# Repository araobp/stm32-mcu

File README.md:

# Application components for STMicro STM32 MCUs

Toolchain: Migrating from TrueSTUDIO+CubeMX to [STM32CubeIDE](https://www.st.com/en/development-tools/stm32cubeide.html)

## Common libraries

### [NUCLEO-F401RE](http://www.st.com/en/evaluation-tools/nucleo-f401re.html) board

- [DCT Type-II implementation on CMSIS-DSP (also works on L4)](./NUCLEO-F401RE/DCT) including a zigzag scan utility function.

## Application components

### [NUCLEO-F401RE](http://www.st.com/en/evaluation-tools/nucleo-f401re.html) board

- [Thermography (infrared array sensor) and rock-paper-scissors recogniton with Keras/TensorFlow](./NUCLEO-F401RE/Thermography)
- [X-CUBE-AI (ML inference on MCU with 2D images from an infrared array sensor)](./NUCLEO-F401RE/AI)
- [X-CUBE-BLE1 (BLE)](./NUCLEO-F401RE/BLE)

### [NUCLEO-L476RG](http://www.st.com/en/evaluation-tools/nucleo-l476rg.html) board

- [HelloWorld](./NUCLEO-L476RG/HelloWorld)
- [GPIO_Interrupt](./NUCLEO-L476RG/GPIO_Interrupt)
- [Clock](./NUCLEO-L476RG/Clock/README.md)
- [CAN](./NUCLEO-L476RG/CAN/README.md)
- [MEMSMIC(MEMS mic expansion board)](./NUCLEO-L476RG/MEMSMIC/README.md)
- [ADC with DMA](./NUCLEO-L476RG/ADC/README.md)
- [DAC with triangular wave and sine wave](./NUCLEO-L476RG/DAC/README.md)
- [Mic->ADC->DAC pipeline](./NUCLEO-L476RG/Mic_ADC_DAC/README.md)
- [Sound Effector](./NUCLEO-L476RG/Sound_Effector)
- [Chirp compression](./NUCLEO-L476RG/Chirp_Compression)

### [NUCLEO-F401RE](http://www.st.com/en/evaluation-tools/nucleo-f401re.html) and [NUCLEO-L476RG](http://www.st.com/en/evaluation-tools/nucleo-l476rg.html) boards

#### Dynamic NFC tags
- [ST25DV04K (NFC) on F401RE](./NUCLEO-F401RE/NFC)
- [ST25DV04K (NFC) on L476RG](./NUCLEO-L476RG/NFC) 

### [STM32F4 Discovery](http://www.st.com/en/evaluation-tools/stm32f4discovery.html) board

- [Camera (CMOS image sensor OV7670)](./STM32F4-Discovery/Camera)
- [BlueSwitch](./STM32F4-Discovery/BlueSwitch)
- [HelloWorld](./STM32F4-Discovery/HelloWorld)
- [LED_blinking](./STM32F4-Discovery/LED_blinking)
- [PWM-output](./STM32F4-Discovery/PWM-output)
- [AudioWeaver](./STM32F4-Discovery/AudioWeaver)

#### printf issue

I managed to support printf on USART2.

Physical configuration:

```
STM32F407
               +------------+
            X 5V            |
GND     ----- GND  FTDI     |
PA3(RX) ----- TX  USB-UART  ===== USB ======> PC
PA2(TX) ----- RX  converter |
               +------------+
```

Include the following snippet in main.c to support printf:

```
int _write(int file, char *pbuf, int len)
{
  HAL_UART_Transmit(&huart2, (uint8_t *)pbuf, len, 1000);
  return len;
}
```

#### PWM test

PWM output (100Hz, 50% duty) to PA8:

## Tips

- [CMSIS DSP RFFT pitfalls](./tips/CMSIS_DSP_RFFT.md)
- [Enabling DSP on STM32](./tips/ENABLE_DSP.md)
- [PCM data resolution on STM32L4 DFSDM](./tips/RESOLUTION.md)
- [Enabling printf on STM32](./tips/ENABLE_PRINTF.md)

## References

### STM32L476 Nucleo-64

- [Schematics](http://www.st.com/resource/en/schematic_pack/nucleo_64pins_sch.zip)
- [Datasheet](http://www.st.com/resource/en/datasheet/stm32l476je.pdf)

### STM32F4 Discovery board

- [Schematics](http://www.st.com/resource/en/schematic_pack/stm32f4discovery_sch.zip)
- [Datasheet](http://www.st.com/resource/en/datasheet/dm00037051.pdf)

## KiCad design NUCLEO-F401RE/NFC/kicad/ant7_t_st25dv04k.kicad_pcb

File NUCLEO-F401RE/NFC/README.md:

# ST25DV04K

This chip ["ST25DV04K"](https://www.st.com/en/nfc/st25dv-i2c-series-dynamic-nfc-tags.html) from STMicro can be used for showing an internal status of a home appliance to the user's smart phone.

[Note] I lately migrated from TrueSTUIO+CubeMX to CubeIDE. The quality of CubeIDE 1.0.0 is NOT good. Some precautions I learned by doing for 24 hours wasting a lot of time:
- Always start a new STM32 project from CubeIDE, do not generate code from CubeMX.
- Do not regenerate code on CubeIDE -- if you need some config modifications, create a new project on CubeIDE again, although it is a waste of time.
- Otherwise, you will face a lot of errors at a build time or a debug time, including communication errors with the targe board over ST-Link.

## Typical operations (my guess)

[1] A smart phone initiates a service.

```
   Sleeping                                         
    [STM32]          [ST25DV]<---RF----[Smart phone] User
      ^               GPO                           
      |                |
      +----------------+
           Interrupt
```

[1b(optional)] The device notifies a BLE central of the RF field change event 

```
       +--------NOTIFY---------------------------->[BLE central]
       |
   [RN4020]                                         
    [STM32]          [ST25DV]<---RF----[Smart phone] User
```

[2] The device prepares a service for the user in a very short time.

```
[Local service function]
       |
       v
    [STM32]          [ST25DV]<---RF----[Smart phone] User
Service preparation  
```

[3] The device provides a service URL to the smartphone.

```
    [STM32]---I2C--->[ST25]----RF--->[Smart phone]----GET---->[Web application server]
                             (URL)
```

[4] The smartphone fetchs the page from a web server.

```
    [STM32]          [ST25]          [Smart phone]<---200 OK--[Web application server]
```

Note: the last data written on the tag (e.g., on EEPROM) will remain even if the battery dies.

## Internal status of home appliance

- Initial setup: URL of its startup manual page
- Serial number (fixed number): URL of a user registration page
- Some additional reference info (content ID) to a base URL: content ID shown on a digital signage currently
- Error code: URL of its trouble shooting page
- etc

In this project, I only support a serial number that is incremented every time the user hold his or her smart phone over the NFC tag. In case of the signage use case, content ID is appended to its base URL as "&ref=".

## Parts

- [Host MCU: NUCLEO F401RE](https://www.st.com/en/evaluation-tools/nucleo-f401re.html)
- [NFC tag: X-NUCLEO-NFC04A1(ST25DV04K)](https://www.st.com/en/ecosystems/x-nucleo-nfc04a1.html)
- [NFC tag: ANT7-T-ST25DV04K](https://www.st.com/en/evaluation-tools/ant7-t-st25dv04k.html)

## Code

### MCU with ST25DV

IDE: CubeIDE from STMicro.

==> **[Code](./stm32)**

- The code supports power management for the MCU.
- The code puts the MCU into sleep after start up, so CubeIDE cannot communicate with the MCU. In this case, hold a smart phone over the antenna to keep the MCU awaken.
- To disable the power management (to use GPO on PA9 as an interrupt to signal RF change to MCU), just comment out the following line:

main.c
```
#define SLEEP_ENABLED
```

**UART commands**

|Command                          |Description                        |
|---------------------------------|-----------------------------------|
|.l                               |Lock RF write (default)            |
|.u                               |Unlock RF write                    |
|.r                               |Reset (and clear EEPROM)           |
|<base url w/o protocol>?loc=<loc>|Write base URL to Area 2 on EEPROM |

Note: The current implementation of local service function just copies the base URL with a serial number, as an internal status of a home appliance, appended to Area 1 on EEPROM.

### HTTPS server for testing the device

==> **[Code](./webapp)**

### Home appliances

==> **[Code](./home_appliances)**

### Arduino shield of ANT7-T-ST25DV04K

I refered to the schematic of X-NUCLEO-NFC04A1(ST25DV04K) to design Arduino shield for ANT7-T-ST25DV04K with some modifications as follows:
- I omitted some small stuff such as bypass capacitors, because the board size is small.
- I chose 10k ohm pull-up registors for I2C. I think 10k ohm is relatively large, but it should work at 400kHz of SCL clock cycle in my experience.
- I chose a 51k ohm pull-up registor for open-drain GPO.

==> **[Circuit](./kicad/ant7_t_st25dv04k.pdf)**

==> **[Universal board](./kicad/arduino_shield_ant7_t_st25dv04k.pdf)**

## A bug in X-CUBE-NFC4/CubeMX

BSP folder is removed whenever code is generated by CubeMX after the initial generation. Copy BSP into the folder manually to cope with the problem.

## Future direction

["ADUX1020"](https://www.analog.com/en/products/adux1020.html) from Analog Devices is very interesting as a very small contactless gester sensing device in combination with dynamic NFC tag (not limited to STMicro's products but also from other makers such as NXP or SONY).

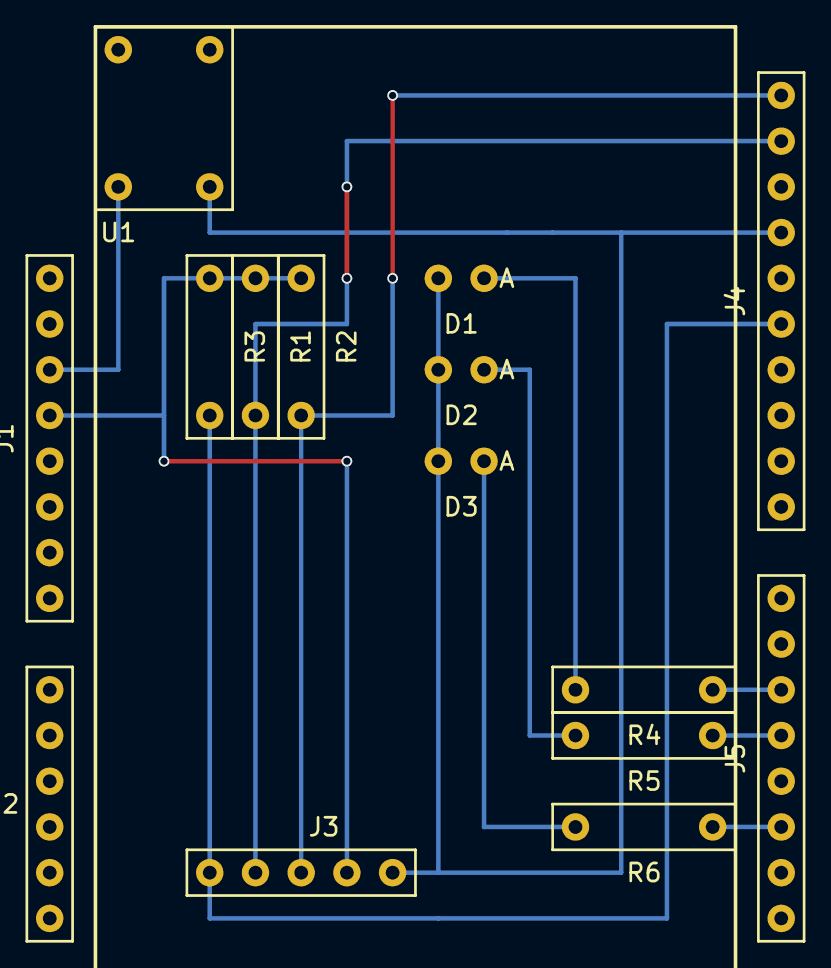
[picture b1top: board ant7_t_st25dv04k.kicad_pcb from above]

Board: 2 copper layers, 15 parts (0 on the bottom side), 12 nets.

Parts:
D1: LED GREEN; LED
D2: LED BLUE; LED
D3: LED RED; LED
J1, J5: Conn_01x08_Male; Pin Header 8P
J2: Conn_01x06_Male; Pin Header 6P
J3: Conn_01x05_Male; Pin_Header_5P
J4: Conn_01x10_Male; Pin Header 10P
R1, R2, R6: 10k; Register
R3, R4, R5: 51k; Register
U1: tactile_sw; tactile_sw_4p

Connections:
+3V3: J1.4, J3.2, R1.1, R2.1, R3.1
GND: D1.1, D2.1, D3.1, J3.1, J4.4, U1.2
unnamed: D1.2, R4.2
unnamed: D2.2, R5.2
unnamed: D3.2, R6.2
unnamed: J1.3, U1.4
unnamed: J3.3, J4.1, R2.2
unnamed: J3.4, J4.2, R1.2
unnamed: J3.5, J4.6, R3.2
unnamed: J5.3, R4.1
unnamed: J5.4, R5.1
unnamed: J5.6, R6.1

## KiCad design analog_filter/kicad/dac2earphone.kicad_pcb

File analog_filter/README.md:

## Analog filter

Some of the applications in this project require an analog filter for DAC to remove quantization noise and to remove DC (AC coupling). The quality of sound is not so good: this filter is just for some experiments on DSP.

- [Circuit simulation (LTspice)](./ltspice)
- [Frequency response (LTspice)](./ltspice/LPF_HPF_for_DAC_and_earphone.pdf)
- [Circuit schematic (KiCad)](./kicad/dac2earphone.pdf)

Input signal before the analog filter:

Output signal after the analog filter:

## Wirling the analog filter to Arduino connector

- Connect PA4 to left-channel pin header,
- Connect PA5 to right-channel pin header,
- Connect GND to GND pin header,
on the analog filter board.

```
                                     [ ]
                                     [ ]
                                     [ ]
                                     [ ]
  [ ]                                [*] PA5(DAC1 OUT2)
  [ ]                                [ ]
  [ ]                                [ ]
  [ ]                                [ ]
  [ ]                                [ ]
  [*] GND                            [ ]
  [ ]
  [ ]                                [ ]
                                     [ ]
  [ ]                                [ ]
  [ ]                                [ ]
  [*] PA4(DAC1 OUT1)                 [ ]
  [ ]                                [ ]
  [ ]                                [ ]
  [ ]                                [ ]
  ```

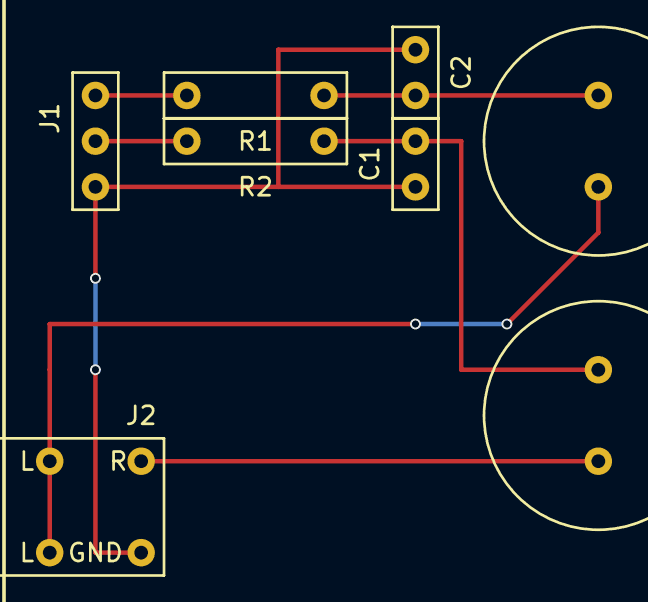
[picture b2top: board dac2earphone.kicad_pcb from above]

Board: 2 copper layers, 8 parts (0 on the bottom side), 7 nets.

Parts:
C1, C2: 0.1u; Capacitor
C3, C4: 220u; audio_capacitor
J1: Conn_01x03_Male; Pin_Header_3P
J2: Conn_01x03_Male; audio_jack_3.5mm
R1, R2: 120; Register

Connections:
GND: C1.2, C2.2, J1.3, J2.1
unnamed: C1.1, C4.2, R2.1
unnamed: C2.1, C3.2, R1.1
unnamed: C3.1, J2.3
unnamed: C4.1, J2.2
unnamed: J1.1, R1.2
unnamed: J1.2, R2.2

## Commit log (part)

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2019-01-06 standard normalization
2019-01-06 add pictures
2019-01-06 CubeMX migration from v5.0.0 to v5.0.1
2019-01-08 DCT Type-II
2019-01-08 DCT Type-II 2D
2019-01-09 DCT Type-II as feature
2019-01-10 Zigzag scan utility
2019-02-13 OV7670 initialization
2019-02-13 expansion board schematic
2019-02-17 QCIF PAL
2019-02-17 Output QCIF raw image to UART
2019-02-22 DCT for detecting edge
2019-03-17 FTDI driver test
2019-04-08 Remove BLE-related projects
2019-04-12 Add RN4020
2019-04-12 Add bluepy
2019-04-13 Add notify example
2019-04-13 RN4020 shield
2019-04-13 remove Wireless folder
2019-04-22 BLE and NFC
2019-04-22 remove
2019-04-22 Rename ENABLE_DSP_AND_PRINTF.md to ENABLE_DSP.md
2019-04-22 Rename PRINTF.md to ENABLE_PRINTF.md
2019-04-22 SensorDemo
2019-04-23 add BLE projects
2019-04-23 Template
2019-05-23 Dynamic NFC project
2019-05-23 add pic
2019-05-27 FTDI skelton
2019-05-27 remove android
2019-05-27 Code for #2
2019-05-29 v-bind:class applied
2019-05-31 Circuit of arduino shield
2019-05-31 schematic update
2019-06-03 CubeIDE 1.0.0's quality is NOT good, took 24 hours to figure out how to fix errors
2019-06-03 Dynamic NFC tag for NULCEO-L476RG
2019-06-08 Support MQTT over SSL/TLS
2019-06-08 Remove BLE gateway to simplify the architecture.
2019-06-08 Fix for #3
